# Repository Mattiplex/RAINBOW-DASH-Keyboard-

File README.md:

# RAINBOW-DASH-KEYBOARD-
A MLP theme KEYBOARD !!!

oh yeah , watch me take on this four day challenge to create this keyboard with no experience. (editing matthew here) so keeb got extended but i miss the deadline so im shipping to STARDANCE. oh well stardance has ended also well better luck at fabricate !!!

# The What,Why and What i learn.  
## The WHAT
RAINBOW DASH KEYBOARD is a 75% and TKL Hybrid MLP theme keyboard. this keyboard features 84 mechanical switches with hot swappable socket ,Backlit south facing RGB LED,Rotary Encoder and a 0.91 inch OLED screen.this keyboard is power by 3rd party Pico clone board with usb-c port. i also design a custom Case that uses a bottom mount system, The case will be 3d printed with FDM technology Using PETG and be painted later using spray paint. The plate will be fabricated using aluminum 6061-T6 Alloy and have an anodized blue and glass bead sanding finish.There's also a custom Knob that will be printed using PLA.

## The WHY   
so this is my first keyboard, so i decide to challenge myself to create something that's distinctly me. something that other people doesn't have and that is functional so a keyboard is fun little challenge.i want to be able look at me keyboard and be reminded of the countless night i spend making this keyboard.  

## What have i LEARN ?  
i learn lots of stuff, first of all is to do tons of research before going through something you're not familiar with. i also how to make a keyboard , how to plan your keyboard before hand so you don't mess up later in your PCB phase. (i learn all of these the hard way).
CAD is a bit harder for me because im such a perfectionist. but everything gets better with the flow of time as you gain experience. now the KEYWORD here is failing. during the whole length of this project , i fail a lot and that's how i learn ,you learn by failing and trying again.

# The PCB 

# The Case 

i used Bottom style mount to house my pcb , since i think it's the most balance layout between sound , cost and complexity . i also made the plate to integrate inside the bottom case so the plate would sit flush in the case. 
* Bottom Case: PLA WHITE
* TOP Case : PLA WHITE
* KEYBOARD PLATE : Laser Cut Aluminum (anodized blue + bead blast)
* CUSTOM Knob : PLA WHITE

# README
3D PRINTING : PRINTING LEGION @raahicheda4 (SG)

# ASSEMBLY Video

# Time   

  | no | desc | Time taken |  
  | -- | ---- | -----------|  
  | 1. | first design session | 14Hour 33Min 58 Sec |   
  | 2. | second design session | 22Hour 17Min 35Sec |  
  | 3. | CAD design session | 24Hour 27Min 46Sec |  
  | 4. | prepping model and inspection | 39Min |
  | - | total time | 62Hour 12Min 58Sec | 

# price 

| No | DESC | USD | 
| -- | ---- | --- |
| 1. | PCB Board (5 piece)| 21.23USD | 
| 1. | 0805 SMD Cap (20 Piece) ELEMENT14 | 6.02$ | 
| 2. | Kalih Hot Swappable socket (110pc) | 6.06$ |
| 3. | 330R resistor 100pc | 1.12$ |
| 4. | 4700R resistor 100pc | 2.45$ |
| 5. | MCP23017 DIP28 2pc | 6.02$ |
| 6. | EC11 Rotary Encoder 1pc | 0.73$ |
| 7. | M2 Heatset Insert L 3mm 50pc  | 1.41$ |
| 8. | M3 Heatset Insert L 3mm 50pc  | 1.47$ |
| 9. | HZYUEGOU M2 hex wafer head screw  5mm 50pc  | 0.94$ |
| 10. | HZUEGOU M3 hex Wafer head screw 20mm 25pc  |  1.11$ |
| 11. | 1N4148 0805 SOD-323 diode 100pc |  0.95$ |
| 12. | SK6812 MINi-E RGB reverse mount 100pc | 5.71$ |
| 13. | Third party Pi-Pico with Usb-c 1pc | 2.57$ |
| 14. | 0.91inch OLED SCREEN 1pc  | 2.36$ |
| 15. | 1mm transparent acrylic sheet 1 pc | 0.92$ |
| 1. | Jaycomia Rainbow PBT Keycaps Set | 20.37$ |
| 2. | Kalih Box Jade Tactile switch (90pc) | 20.49$ |
| 3. | Durock Stabilizer V3 set 4(2u) 1(6.25u) | 18.26$ |
| 4. | Fancy rainbow coiled Usb-C cable with aviator connector | 7.97$ |
| 3. | Shipping Fee (ALIEXPRESS) | 1.58$ |
| 4. | Shipping Fee (ELEMENT14) | None |
| 5. | TAX (ALIEXPRESS) | 10.93$ | 
| 6. | Extra 5$ for daily price fluctuation Aliexpress | 5$ | 
| 1. | Top Case,bottom case & custom knob (Printing Legion) | 30$ |
| 2. | aluminum Plate (PCBWAY) | 39.77$ | 
| 3. | shipping Fee (Printing Legion) | 10$ |
| 4. | shipping Fee (PCBWAY) | none (air freight) |   
| - | Total | 225.44$ | 

## excluded stuff (coz it's expensive enough alr)
* spray paint & primer 
* high grit sand paper 
* solder and flux

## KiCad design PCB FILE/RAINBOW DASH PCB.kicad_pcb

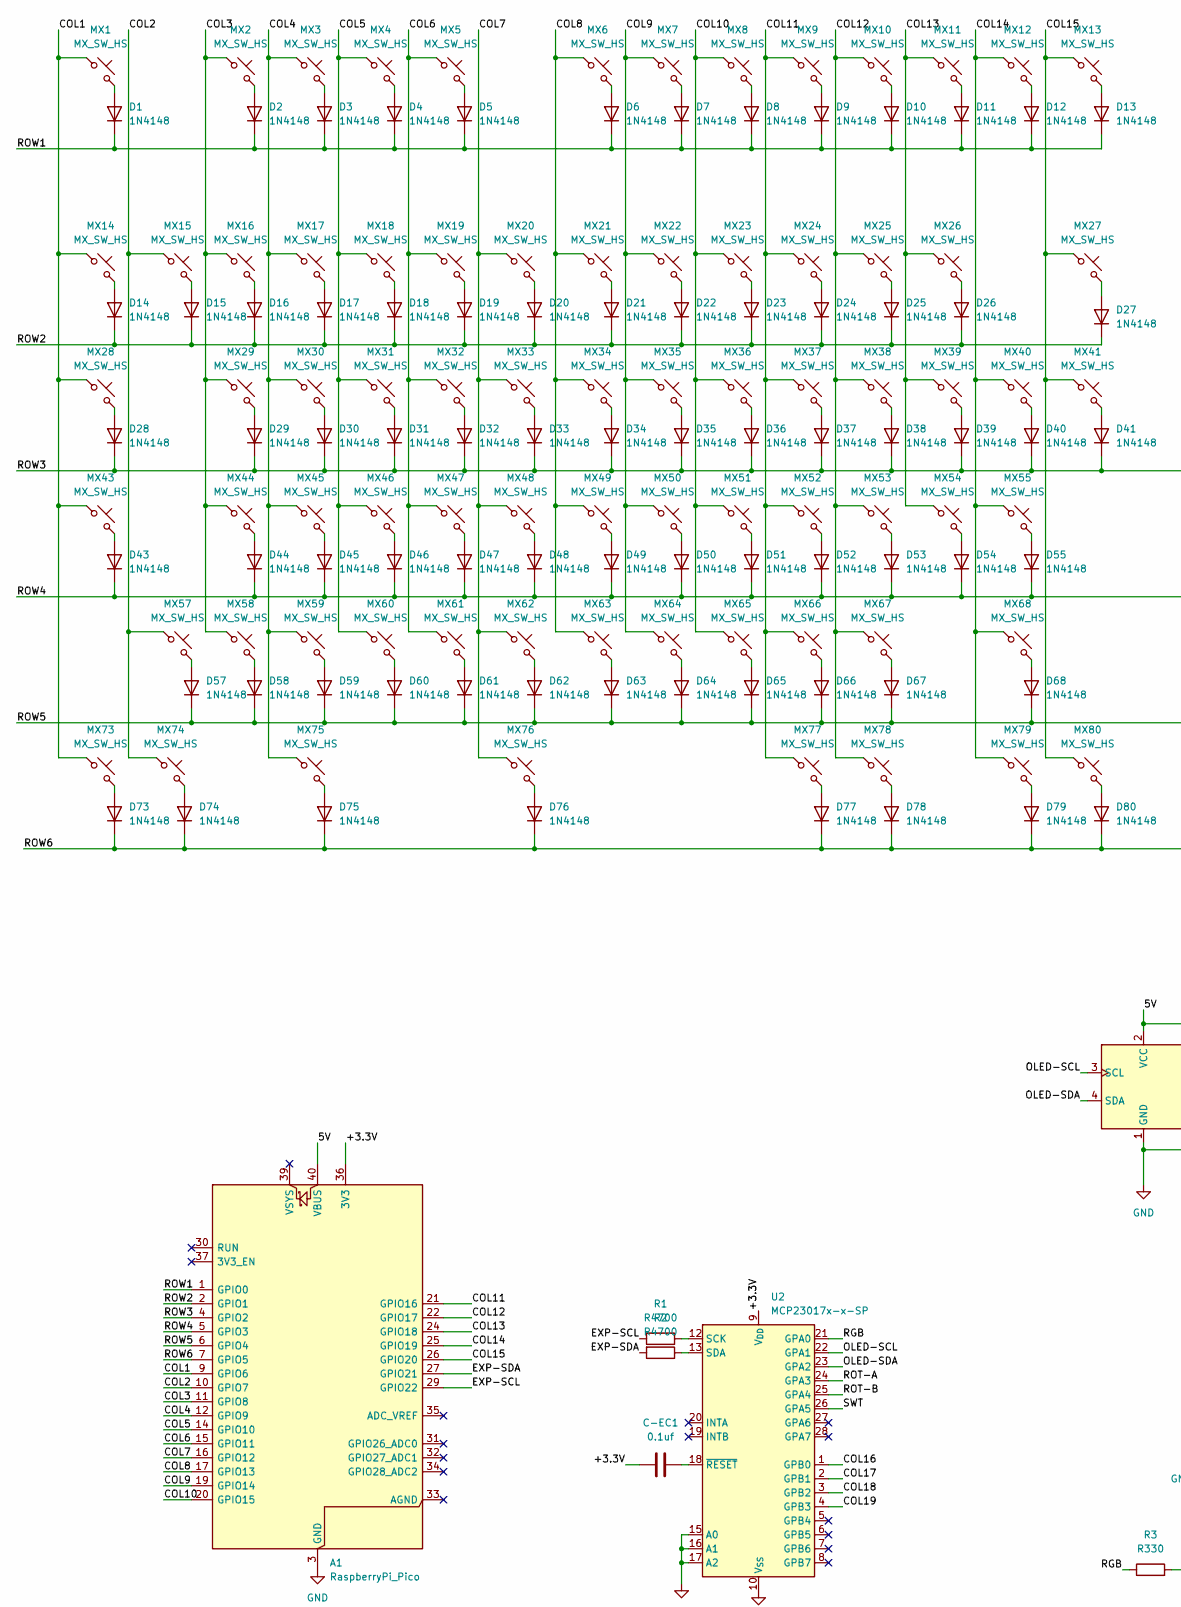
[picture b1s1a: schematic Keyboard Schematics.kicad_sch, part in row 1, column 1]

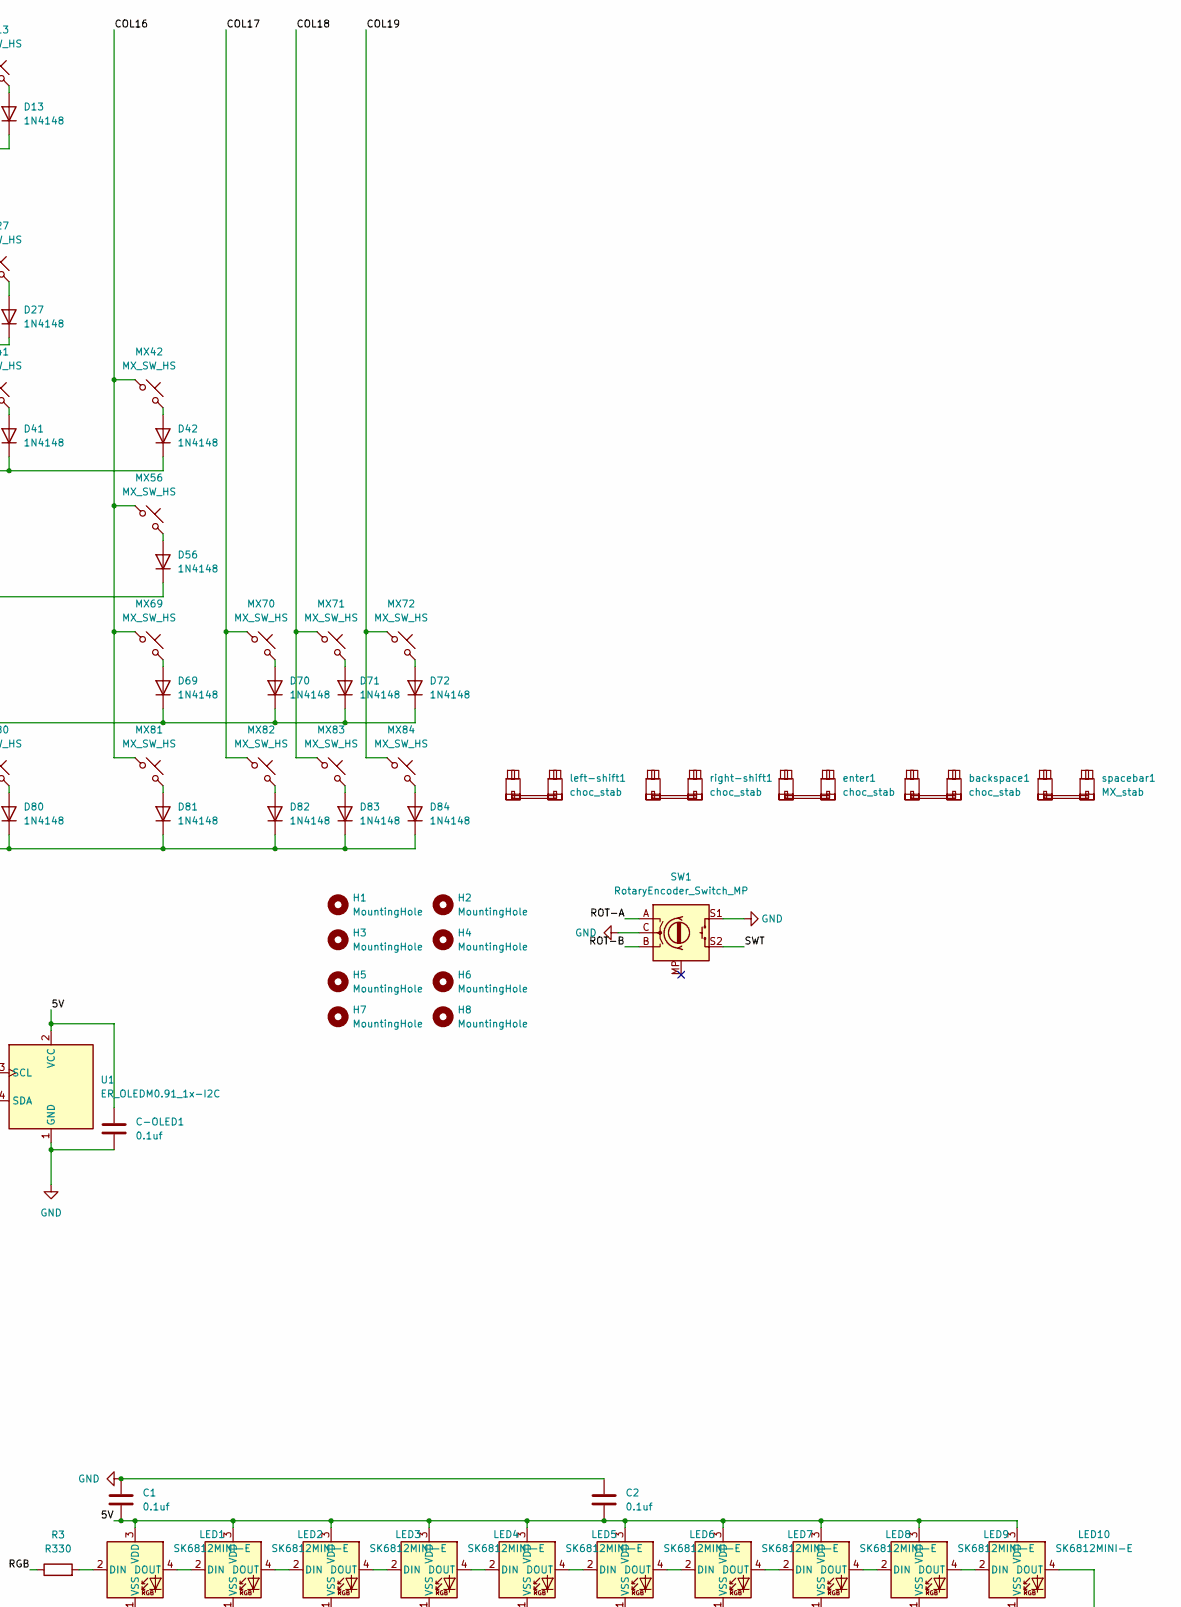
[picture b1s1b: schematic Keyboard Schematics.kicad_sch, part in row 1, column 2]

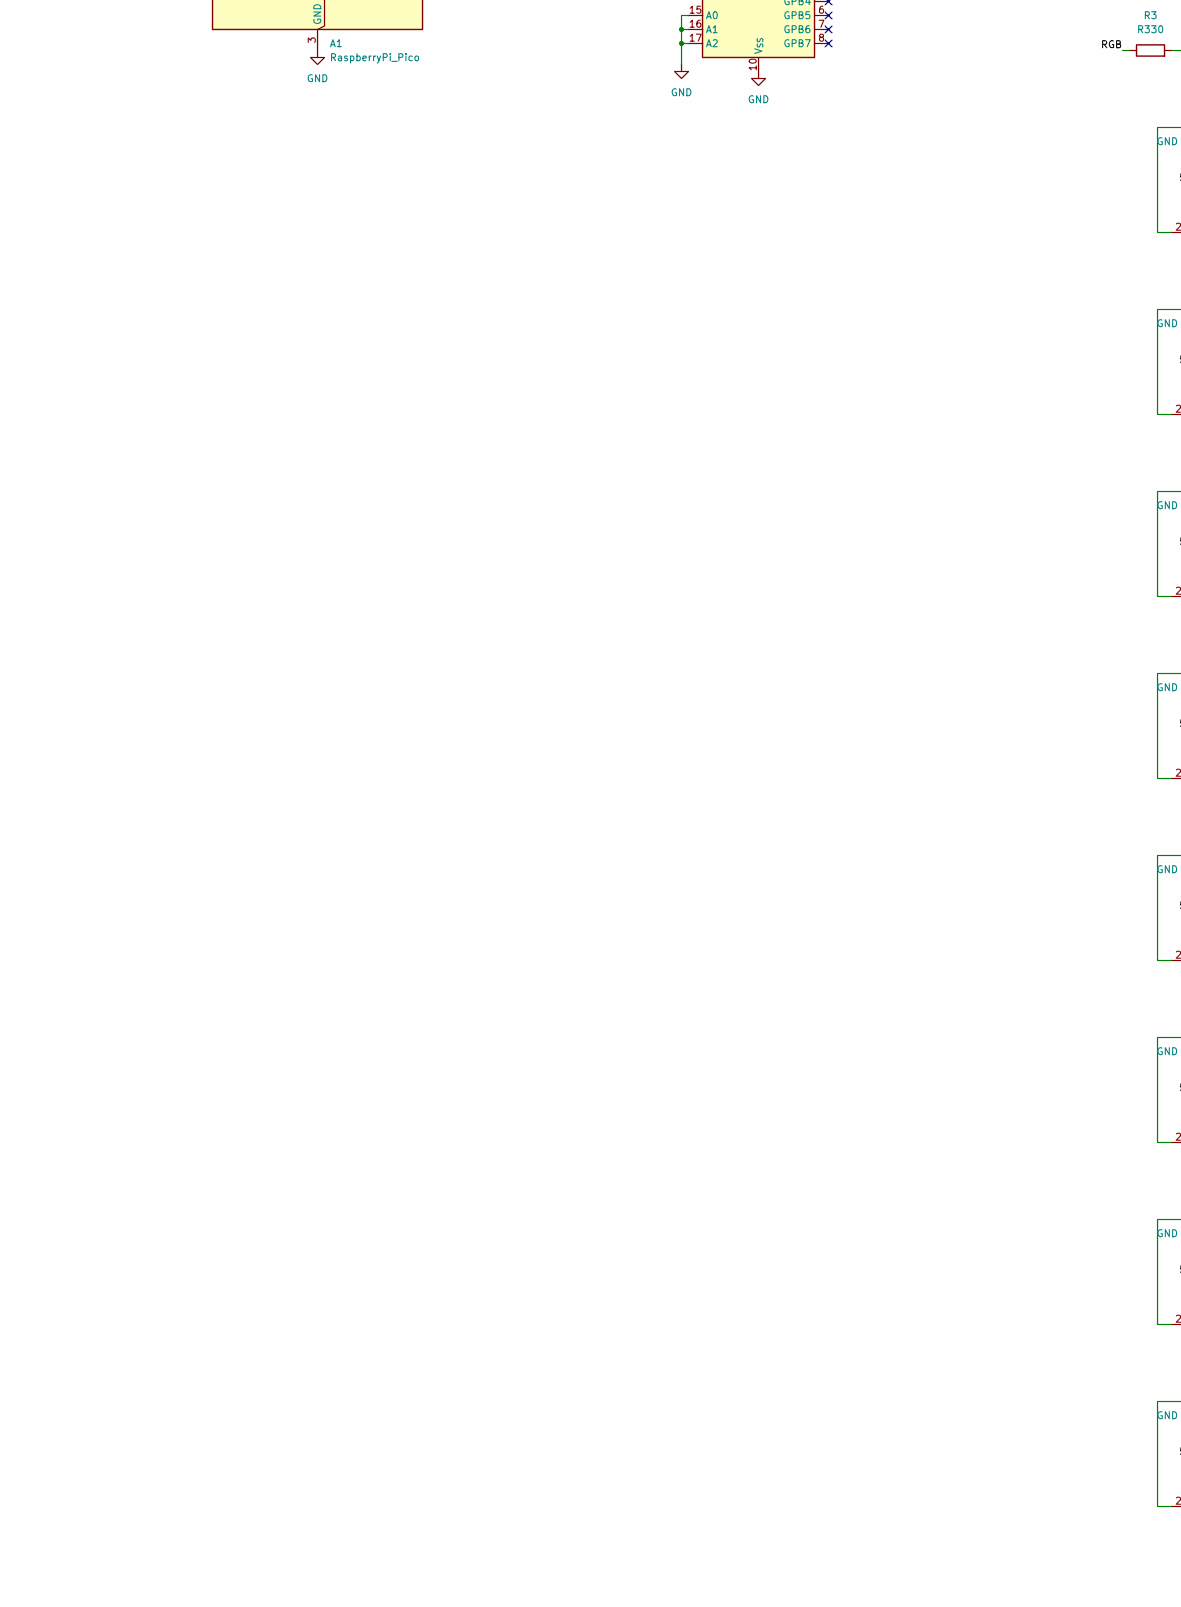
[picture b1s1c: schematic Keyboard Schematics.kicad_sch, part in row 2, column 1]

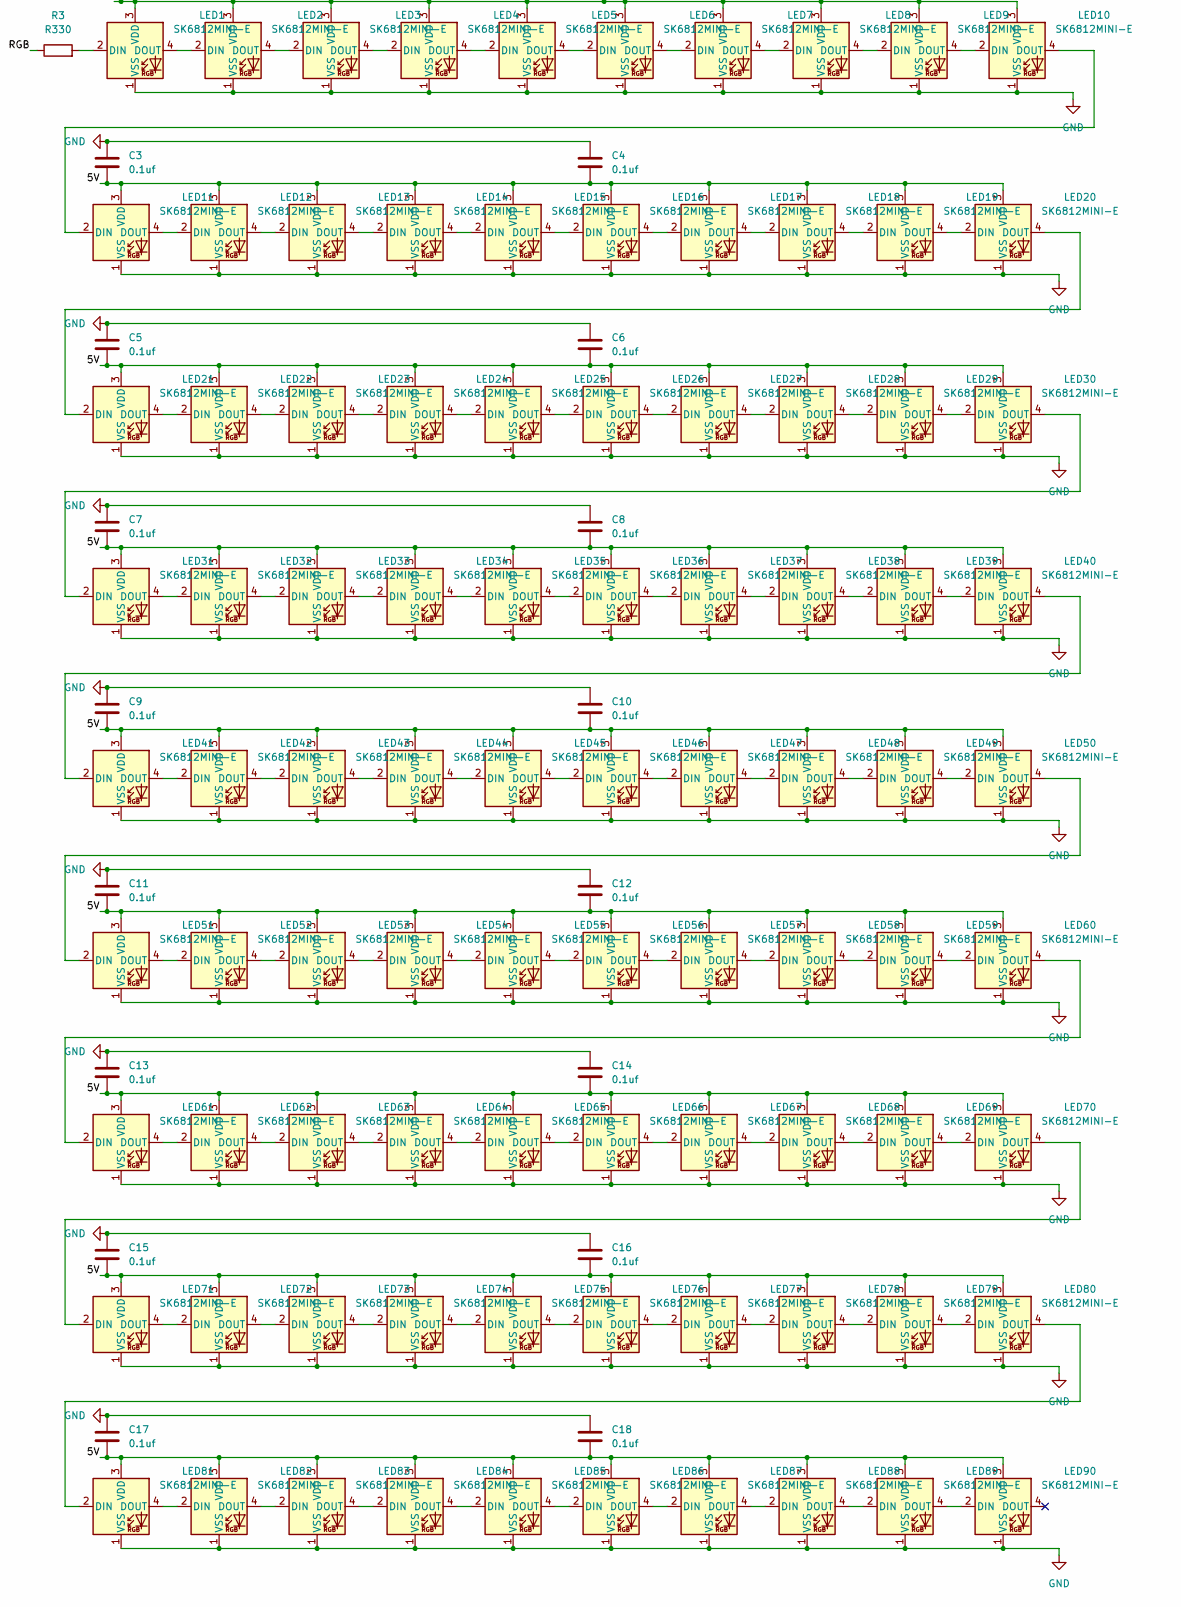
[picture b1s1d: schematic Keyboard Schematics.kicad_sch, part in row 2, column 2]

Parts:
A1: RaspberryPi_Pico; RaspberryPi_Pico_Common_THT
C1, C2, C3, C4, C5, C6, C7, C8, C9, C10, C11, C12, C13, C14, C15, C16, C17, C18: 0.1uf; C_0805_2012Metric_Pad1.18x1.45mm_HandSolder
C-EC1: 0.1uf; C_0805_2012Metric_Pad1.18x1.45mm_HandSolder
C-OLED1: 0.1uf; C_0805_2012Metric_Pad1.18x1.45mm_HandSolder
D1, D2, D3, D4, D5, D6, D7, D8, D9, D10, D11, D12, D13, D14, D15, D16, D17, D18, D19, D20, D21, D22, D23, D24, D25, D26, D27, D28, D29, D30, D31, D32, D33, D34, D35, D36, D37, D38, D39, D40, D41, D42, D43, D44, D45, D46, D47, D48, D49, D50, D51, D52, D53, D54, D55, D56, D57, D58, D59, D60, D61, D62, D63, D64, D65, D66, D67, D68, D69, D70, D71, D72, D73, D74, D75, D76, D77, D78, D79, D80, D81, D82, D83, D84: 1N4148; D_0805_2012Metric
H1, H2, H3, H4, H5, H6, H7, H8: MountingHole; MountingHole_2.2mm_M2
LED1, LED2, LED3, LED4, LED5, LED6, LED7, LED8, LED9, LED10, LED11, LED12, LED13, LED14, LED15, LED16, LED17, LED18, LED19, LED20, LED21, LED22, LED23, LED24, LED25, LED26, LED27, LED28, LED29, LED30, LED31, LED32, LED33, LED34, LED35, LED36, LED37, LED38, LED39, LED40, LED41, LED42, LED43, LED44, LED45, LED46, LED47, LED48, LED49, LED50, LED51, LED52, LED53, LED54, LED55, LED56, LED57, LED58, LED59, LED60, LED61, LED62, LED63, LED64, LED65, LED66, LED67, LED68, LED69, LED70, LED71, LED72, LED73, LED74, LED75, LED76, LED77, LED78, LED79, LED80, LED81, LED82, LED83, LED84, LED85, LED86, LED87, LED88, LED89, LED90: SK6812MINI-E; LED_SK6812MINI-E_3.2x2.8mm_P1.5mm_ReverseMount
MX1, MX2, MX3, MX4, MX5, MX6, MX7, MX8, MX9, MX10, MX11, MX12, MX13, MX14, MX15, MX16, MX17, MX18, MX19, MX20, MX21, MX22, MX23, MX24, MX25, MX26, MX27, MX28, MX29, MX30, MX31, MX32, MX33, MX34, MX35, MX36, MX37, MX38, MX39, MX40, MX41, MX42, MX43, MX44, MX45, MX46, MX47, MX48, MX49, MX50, MX51, MX52, MX53, MX54, MX55, MX56, MX57, MX58, MX59, MX60, MX61, MX62, MX63, MX64, MX65, MX66, MX67, MX68, MX69, MX70, MX71, MX72, MX73, MX74, MX75, MX76, MX77, MX78, MX79, MX80, MX81, MX82, MX83, MX84: MX_SW_HS; SW_MX_HS_CPG151101S11_1u
R1, R2: R4700; R_Axial_DIN0207_L6.3mm_D2.5mm_P10.16mm_Horizontal
R3: R330; R_Axial_DIN0207_L6.3mm_D2.5mm_P10.16mm_Horizontal
SW1: RotaryEncoder_Switch_MP; ROT_Alps_EC11E-Switch
U1: ER_OLEDM0.91_1x-I2C
U2: MCP23017x-x-SP; DIP-28_W7.62mm_LongPads
backspace1: choc_stab; STAB_MX_2u
enter1: choc_stab; STAB_MX_2.25u
left-shift1: choc_stab; STAB_MX_2.25u
right-shift1: choc_stab; STAB_MX_2.75u
spacebar1: MX_stab; STAB_MX_6.25u

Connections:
/5V: A1.40 (VBUS), C1.1, C2.1, C3.1, C4.1, C5.1, C6.1, C7.1, C8.1, C9.1, C10.1, C11.1, C12.1, C13.1, C14.1, C15.1, C16.1, C17.1, C18.1, C-OLED1.1, LED1.3 (VDD), LED2.3 (VDD), LED3.3 (VDD), LED4.3 (VDD), LED5.3 (VDD), LED6.3 (VDD), LED7.3 (VDD), LED8.3 (VDD), LED9.3 (VDD), LED10.3 (VDD), LED11.3 (VDD), LED12.3 (VDD), LED13.3 (VDD), LED14.3 (VDD), LED15.3 (VDD), LED16.3 (VDD), LED17.3 (VDD), LED18.3 (VDD), LED19.3 (VDD), LED20.3 (VDD), LED21.3 (VDD), LED22.3 (VDD), LED23.3 (VDD), LED24.3 (VDD), LED25.3 (VDD), LED26.3 (VDD), LED27.3 (VDD), LED28.3 (VDD), LED29.3 (VDD), LED30.3 (VDD), LED31.3 (VDD), LED32.3 (VDD), LED33.3 (VDD), LED34.3 (VDD), LED35.3 (VDD), LED36.3 (VDD), LED37.3 (VDD), LED38.3 (VDD), LED39.3 (VDD), LED40.3 (VDD), LED41.3 (VDD), LED42.3 (VDD), LED43.3 (VDD), LED44.3 (VDD), LED45.3 (VDD), LED46.3 (VDD), LED47.3 (VDD), LED48.3 (VDD), LED49.3 (VDD), LED50.3 (VDD), LED51.3 (VDD), LED52.3 (VDD), LED53.3 (VDD), LED54.3 (VDD), LED55.3 (VDD), LED56.3 (VDD), LED57.3 (VDD), LED58.3 (VDD), LED59.3 (VDD), LED60.3 (VDD), LED61.3 (VDD), LED62.3 (VDD), LED63.3 (VDD), LED64.3 (VDD), LED65.3 (VDD), LED66.3 (VDD), LED67.3 (VDD), LED68.3 (VDD), LED69.3 (VDD), LED70.3 (VDD), LED71.3 (VDD), LED72.3 (VDD), LED73.3 (VDD), LED74.3 (VDD), LED75.3 (VDD), LED76.3 (VDD), LED77.3 (VDD), LED78.3 (VDD), LED79.3 (VDD), LED80.3 (VDD), LED81.3 (VDD), LED82.3 (VDD), LED83.3 (VDD), LED84.3 (VDD), LED85.3 (VDD), LED86.3 (VDD), LED87.3 (VDD), LED88.3 (VDD), LED89.3 (VDD), LED90.3 (VDD), U1.2 (VCC)
/+3.3V: A1.36 (3V3), C-EC1.1, U2.9 (V_{DD})
/COL1: A1.9 (GPIO6), MX1.1, MX14.1, MX28.1, MX43.1, MX73.1
/COL2: A1.10 (GPIO7), MX15.1, MX57.1, MX74.1
/COL3: A1.11 (GPIO8), MX2.1, MX16.1, MX29.1, MX44.1, MX58.1
/COL4: A1.12 (GPIO9), MX3.1, MX17.1, MX30.1, MX45.1, MX59.1, MX75.1
/COL5: A1.14 (GPIO10), MX4.1, MX18.1, MX31.1, MX46.1, MX60.1
/COL6: A1.15 (GPIO11), MX5.1, MX19.1, MX32.1, MX47.1, MX61.1
/COL7: A1.16 (GPIO12), MX20.1, MX33.1, MX48.1, MX62.1, MX76.1
/COL8: A1.17 (GPIO13), MX6.1, MX21.1, MX34.1, MX49.1, MX63.1
/COL9: A1.19 (GPIO14), MX7.1, MX22.1, MX35.1, MX50.1, MX64.1
/COL10: A1.20 (GPIO15), MX8.1, MX23.1, MX36.1, MX51.1, MX65.1
/COL11: A1.21 (GPIO16), MX9.1, MX24.1, MX37.1, MX52.1, MX66.1, MX77.1
/COL12: A1.22 (GPIO17), MX10.1, MX25.1, MX38.1, MX53.1, MX67.1, MX78.1
/COL13: A1.24 (GPIO18), MX11.1, MX26.1, MX39.1, MX54.1
/COL14: A1.25 (GPIO19), MX12.1, MX40.1, MX55.1, MX68.1, MX79.1
/COL15: A1.26 (GPIO20), MX13.1, MX27.1, MX41.1, MX80.1
/COL16: MX42.1, MX56.1, MX69.1, MX81.1, U2.1 (GPB0)
/COL17: MX70.1, MX82.1, U2.2 (GPB1)
/COL18: MX71.1, MX83.1, U2.3 (GPB2)
/COL19: MX72.1, MX84.1, U2.4 (GPB3)
/EXP-SCL: A1.29 (GPIO22), R1.2
/EXP-SDA: A1.27 (GPIO21), R2.2
/OLED-SCL: U1.3 (SCL), U2.22 (GPA1)
/OLED-SDA: U1.4 (SDA), U2.23 (GPA2)
/RGB: R3.1, U2.21 (GPA0)
/ROT-A: SW1.A, U2.24 (GPA3)
/ROT-B: SW1.B, U2.25 (GPA4)
/ROW1: A1.1 (GPIO0), D1.1 (K), D2.1 (K), D3.1 (K), D4.1 (K), D5.1 (K), D6.1 (K), D7.1 (K), D8.1 (K), D9.1 (K), D10.1 (K), D11.1 (K), D12.1 (K), D13.1 (K)
/ROW2: A1.2 (GPIO1), D14.1 (K), D15.1 (K), D16.1 (K), D17.1 (K), D18.1 (K), D19.1 (K), D20.1 (K), D21.1 (K), D22.1 (K), D23.1 (K), D24.1 (K), D25.1 (K), D26.1 (K), D27.1 (K)
/ROW3: A1.4 (GPIO2), D28.1 (K), D29.1 (K), D30.1 (K), D31.1 (K), D32.1 (K), D33.1 (K), D34.1 (K), D35.1 (K), D36.1 (K), D37.1 (K), D38.1 (K), D39.1 (K), D40.1 (K), D41.1 (K), D42.1 (K)
/ROW4: A1.5 (GPIO3), D43.1 (K), D44.1 (K), D45.1 (K), D46.1 (K), D47.1 (K), D48.1 (K), D49.1 (K), D50.1 (K), D51.1 (K), D52.1 (K), D53.1 (K), D54.1 (K), D55.1 (K), D56.1 (K)
/ROW5: A1.6 (GPIO4), D57.1 (K), D58.1 (K), D59.1 (K), D60.1 (K), D61.1 (K), D62.1 (K), D63.1 (K), D64.1 (K), D65.1 (K), D66.1 (K), D67.1 (K), D68.1 (K), D69.1 (K), D70.1 (K), D71.1 (K), D72.1 (K)
/ROW6: A1.7 (GPIO5), D73.1 (K), D74.1 (K), D75.1 (K), D76.1 (K), D77.1 (K), D78.1 (K), D79.1 (K), D80.1 (K), D81.1 (K), D82.1 (K), D83.1 (K), D84.1 (K)
/SWT: SW1.S2, U2.26 (GPA5)
GND: A1.3 (GND), A1.8 (GND), A1.13 (GND), A1.18 (GND), A1.23 (GND), A1.28 (GND), A1.38 (GND), C1.2, C2.2, C3.2, C4.2, C5.2, C6.2, C7.2, C8.2, C9.2, C10.2, C11.2, C12.2, C13.2, C14.2, C15.2, C16.2, C17.2, C18.2, C-OLED1.2, LED1.1 (VSS), LED2.1 (VSS), LED3.1 (VSS), LED4.1 (VSS), LED5.1 (VSS), LED6.1 (VSS), LED7.1 (VSS), LED8.1 (VSS), LED9.1 (VSS), LED10.1 (VSS), LED11.1 (VSS), LED12.1 (VSS), LED13.1 (VSS), LED14.1 (VSS), LED15.1 (VSS), LED16.1 (VSS), LED17.1 (VSS), LED18.1 (VSS), LED19.1 (VSS), LED20.1 (VSS), LED21.1 (VSS), LED22.1 (VSS), LED23.1 (VSS), LED24.1 (VSS), LED25.1 (VSS), LED26.1 (VSS), LED27.1 (VSS), LED28.1 (VSS), LED29.1 (VSS), LED30.1 (VSS), LED31.1 (VSS), LED32.1 (VSS), LED33.1 (VSS), LED34.1 (VSS), LED35.1 (VSS), LED36.1 (VSS), LED37.1 (VSS), LED38.1 (VSS), LED39.1 (VSS), LED40.1 (VSS), LED41.1 (VSS), LED42.1 (VSS), LED43.1 (VSS), LED44.1 (VSS), LED45.1 (VSS), LED46.1 (VSS), LED47.1 (VSS), LED48.1 (VSS), LED49.1 (VSS), LED50.1 (VSS), LED51.1 (VSS), LED52.1 (VSS), LED53.1 (VSS), LED54.1 (VSS), LED55.1 (VSS), LED56.1 (VSS), LED57.1 (VSS), LED58.1 (VSS), LED59.1 (VSS), LED60.1 (VSS), LED61.1 (VSS), LED62.1 (VSS), LED63.1 (VSS), LED64.1 (VSS), LED65.1 (VSS), LED66.1 (VSS), LED67.1 (VSS), LED68.1 (VSS), LED69.1 (VSS), LED70.1 (VSS), LED71.1 (VSS), LED72.1 (VSS), LED73.1 (VSS), LED74.1 (VSS), LED75.1 (VSS), LED76.1 (VSS), LED77.1 (VSS), LED78.1 (VSS), LED79.1 (VSS), LED80.1 (VSS), LED81.1 (VSS), LED82.1 (VSS), LED83.1 (VSS), LED84.1 (VSS), LED85.1 (VSS), LED86.1 (VSS), LED87.1 (VSS), LED88.1 (VSS), LED89.1 (VSS), LED90.1 (VSS), SW1.C, SW1.S1, U1.1 (GND), U2.10 (V_{SS}), U2.15 (A0), U2.16 (A1), U2.17 (A2)
unnamed: D1.2 (A), MX1.2
unnamed: D2.2 (A), MX2.2
unnamed: D3.2 (A), MX3.2
unnamed: D4.2 (A), MX4.2
unnamed: D5.2 (A), MX5.2
unnamed: D6.2 (A), MX6.2
unnamed: D7.2 (A), MX7.2
unnamed: D8.2 (A), MX8.2
unnamed: D9.2 (A), MX9.2
unnamed: D10.2 (A), MX10.2
unnamed: D11.2 (A), MX11.2
unnamed: D12.2 (A), MX12.2
unnamed: D13.2 (A), MX13.2
unnamed: D14.2 (A), MX14.2
unnamed: D15.2 (A), MX15.2
unnamed: D16.2 (A), MX16.2
unnamed: D17.2 (A), MX17.2
unnamed: D18.2 (A), MX18.2
unnamed: D19.2 (A), MX19.2
unnamed: D20.2 (A), MX20.2
unnamed: D21.2 (A), MX21.2
unnamed: D22.2 (A), MX22.2
unnamed: D23.2 (A), MX23.2
unnamed: D24.2 (A), MX24.2
unnamed: D25.2 (A), MX25.2
unnamed: D26.2 (A), MX26.2
unnamed: D27.2 (A), MX27.2
unnamed: D28.2 (A), MX28.2
unnamed: D29.2 (A), MX29.2
unnamed: D30.2 (A), MX30.2
unnamed: D31.2 (A), MX31.2
unnamed: D32.2 (A), MX32.2
unnamed: D33.2 (A), MX33.2
unnamed: D34.2 (A), MX34.2
unnamed: D35.2 (A), MX35.2
unnamed: D36.2 (A), MX36.2
unnamed: D37.2 (A), MX37.2
unnamed: D38.2 (A), MX38.2
unnamed: D39.2 (A), MX39.2
unnamed: D40.2 (A), MX40.2
unnamed: D41.2 (A), MX41.2
unnamed: D42.2 (A), MX42.2
unnamed: D43.2 (A), MX43.2
unnamed: D44.2 (A), MX44.2
unnamed: D45.2 (A), MX45.2
unnamed: D46.2 (A), MX46.2
unnamed: D47.2 (A), MX47.2
unnamed: D48.2 (A), MX48.2
unnamed: D49.2 (A), MX49.2
unnamed: D50.2 (A), MX50.2
unnamed: D51.2 (A), MX51.2
unnamed: D52.2 (A), MX52.2
unnamed: D53.2 (A), MX53.2
unnamed: D54.2 (A), MX54.2
unnamed: D55.2 (A), MX55.2
unnamed: D56.2 (A), MX56.2
unnamed: D57.2 (A), MX57.2
unnamed: D58.2 (A), MX58.2
unnamed: D59.2 (A), MX59.2
unnamed: D60.2 (A), MX60.2
unnamed: D61.2 (A), MX61.2
unnamed: D62.2 (A), MX62.2
unnamed: D63.2 (A), MX63.2
unnamed: D64.2 (A), MX64.2
unnamed: D65.2 (A), MX65.2
unnamed: D66.2 (A), MX66.2
unnamed: D67.2 (A), MX67.2
unnamed: D68.2 (A), MX68.2
unnamed: D69.2 (A), MX69.2
unnamed: D70.2 (A), MX70.2
unnamed: D71.2 (A), MX71.2
unnamed: D72.2 (A), MX72.2
unnamed: D73.2 (A), MX73.2
unnamed: D74.2 (A), MX74.2
unnamed: D75.2 (A), MX75.2
unnamed: D76.2 (A), MX76.2
unnamed: D77.2 (A), MX77.2
unnamed: D78.2 (A), MX78.2
unnamed: D79.2 (A), MX79.2
unnamed: D80.2 (A), MX80.2
unnamed: D81.2 (A), MX81.2
unnamed: D82.2 (A), MX82.2
unnamed: D83.2 (A), MX83.2
unnamed: D84.2 (A), MX84.2
unnamed: LED1.2 (DIN), R3.2
unnamed: LED1.4 (DOUT), LED2.2 (DIN)
unnamed: LED2.4 (DOUT), LED3.2 (DIN)
unnamed: LED3.4 (DOUT), LED4.2 (DIN)
unnamed: LED4.4 (DOUT), LED5.2 (DIN)
unnamed: LED5.4 (DOUT), LED6.2 (DIN)
unnamed: LED6.4 (DOUT), LED7.2 (DIN)
unnamed: LED7.4 (DOUT), LED8.2 (DIN)
unnamed: LED8.4 (DOUT), LED9.2 (DIN)
unnamed: LED9.4 (DOUT), LED10.2 (DIN)
unnamed: LED10.4 (DOUT), LED11.2 (DIN)
unnamed: LED11.4 (DOUT), LED12.2 (DIN)
unnamed: LED12.4 (DOUT), LED13.2 (DIN)
unnamed: LED13.4 (DOUT), LED14.2 (DIN)
unnamed: LED14.4 (DOUT), LED15.2 (DIN)
unnamed: LED15.4 (DOUT), LED16.2 (DIN)
unnamed: LED16.4 (DOUT), LED17.2 (DIN)
unnamed: LED17.4 (DOUT), LED18.2 (DIN)
unnamed: LED18.4 (DOUT), LED19.2 (DIN)
unnamed: LED19.4 (DOUT), LED20.2 (DIN)
unnamed: LED20.4 (DOUT), LED21.2 (DIN)
unnamed: LED21.4 (DOUT), LED22.2 (DIN)
unnamed: LED22.4 (DOUT), LED23.2 (DIN)
unnamed: LED23.4 (DOUT), LED24.2 (DIN)
unnamed: LED24.4 (DOUT), LED25.2 (DIN)
unnamed: LED25.4 (DOUT), LED26.2 (DIN)
unnamed: LED26.4 (DOUT), LED27.2 (DIN)
unnamed: LED27.4 (DOUT), LED28.2 (DIN)
unnamed: LED28.4 (DOUT), LED29.2 (DIN)
unnamed: LED29.4 (DOUT), LED30.2 (DIN)
unnamed: LED30.4 (DOUT), LED31.2 (DIN)
unnamed: LED31.4 (DOUT), LED32.2 (DIN)
unnamed: LED32.4 (DOUT), LED33.2 (DIN)
unnamed: LED33.4 (DOUT), LED34.2 (DIN)
unnamed: LED34.4 (DOUT), LED35.2 (DIN)
unnamed: LED35.4 (DOUT), LED36.2 (DIN)
unnamed: LED36.4 (DOUT), LED37.2 (DIN)
unnamed: LED37.4 (DOUT), LED38.2 (DIN)
unnamed: LED38.4 (DOUT), LED39.2 (DIN)
unnamed: LED39.4 (DOUT), LED40.2 (DIN)
unnamed: LED40.4 (DOUT), LED41.2 (DIN)
unnamed: LED41.4 (DOUT), LED42.2 (DIN)
unnamed: LED42.4 (DOUT), LED43.2 (DIN)
unnamed: LED43.4 (DOUT), LED44.2 (DIN)
unnamed: LED44.4 (DOUT), LED45.2 (DIN)
unnamed: LED45.4 (DOUT), LED46.2 (DIN)
unnamed: LED46.4 (DOUT), LED47.2 (DIN)
unnamed: LED47.4 (DOUT), LED48.2 (DIN)
unnamed: LED48.4 (DOUT), LED49.2 (DIN)
unnamed: LED49.4 (DOUT), LED50.2 (DIN)
unnamed: LED50.4 (DOUT), LED51.2 (DIN)
unnamed: LED51.4 (DOUT), LED52.2 (DIN)
unnamed: LED52.4 (DOUT), LED53.2 (DIN)
unnamed: LED53.4 (DOUT), LED54.2 (DIN)
unnamed: LED54.4 (DOUT), LED55.2 (DIN)
unnamed: LED55.4 (DOUT), LED56.2 (DIN)
unnamed: LED56.4 (DOUT), LED57.2 (DIN)
unnamed: LED57.4 (DOUT), LED58.2 (DIN)
unnamed: LED58.4 (DOUT), LED59.2 (DIN)
unnamed: LED59.4 (DOUT), LED60.2 (DIN)
unnamed: LED60.4 (DOUT), LED61.2 (DIN)
unnamed: LED61.4 (DOUT), LED62.2 (DIN)
unnamed: LED62.4 (DOUT), LED63.2 (DIN)
unnamed: LED63.4 (DOUT), LED64.2 (DIN)
unnamed: LED64.4 (DOUT), LED65.2 (DIN)
unnamed: LED65.4 (DOUT), LED66.2 (DIN)
unnamed: LED66.4 (DOUT), LED67.2 (DIN)
unnamed: LED67.4 (DOUT), LED68.2 (DIN)
unnamed: LED68.4 (DOUT), LED69.2 (DIN)
unnamed: LED69.4 (DOUT), LED70.2 (DIN)
unnamed: LED70.4 (DOUT), LED71.2 (DIN)
unnamed: LED71.4 (DOUT), LED72.2 (DIN)
unnamed: LED72.4 (DOUT), LED73.2 (DIN)
unnamed: LED73.4 (DOUT), LED74.2 (DIN)
unnamed: LED74.4 (DOUT), LED75.2 (DIN)
unnamed: LED75.4 (DOUT), LED76.2 (DIN)
unnamed: LED76.4 (DOUT), LED77.2 (DIN)
unnamed: LED77.4 (DOUT), LED78.2 (DIN)
unnamed: LED78.4 (DOUT), LED79.2 (DIN)
unnamed: LED79.4 (DOUT), LED80.2 (DIN)
unnamed: LED80.4 (DOUT), LED81.2 (DIN)
unnamed: LED81.4 (DOUT), LED82.2 (DIN)
unnamed: LED82.4 (DOUT), LED83.2 (DIN)
unnamed: LED83.4 (DOUT), LED84.2 (DIN)
unnamed: LED84.4 (DOUT), LED85.2 (DIN)
unnamed: LED85.4 (DOUT), LED86.2 (DIN)
unnamed: LED86.4 (DOUT), LED87.2 (DIN)
unnamed: LED87.4 (DOUT), LED88.2 (DIN)
unnamed: LED88.4 (DOUT), LED89.2 (DIN)
unnamed: LED89.4 (DOUT), LED90.2 (DIN)
unnamed: R1.1, U2.12 (SCK)
unnamed: R2.1, U2.13 (SDA)
unnamed: C-EC1.2, U2.18 (~RESET)

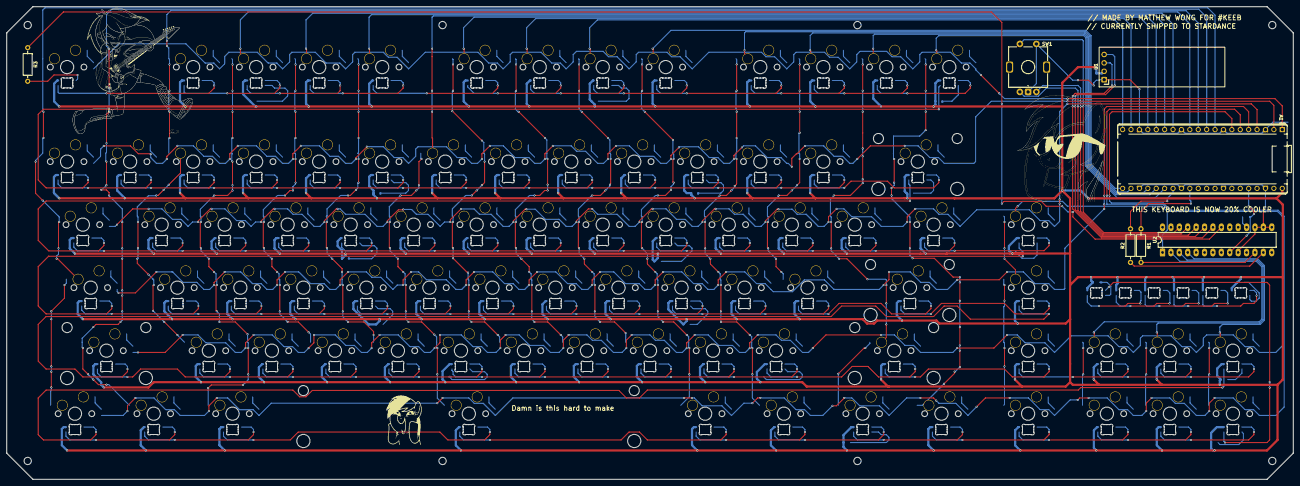
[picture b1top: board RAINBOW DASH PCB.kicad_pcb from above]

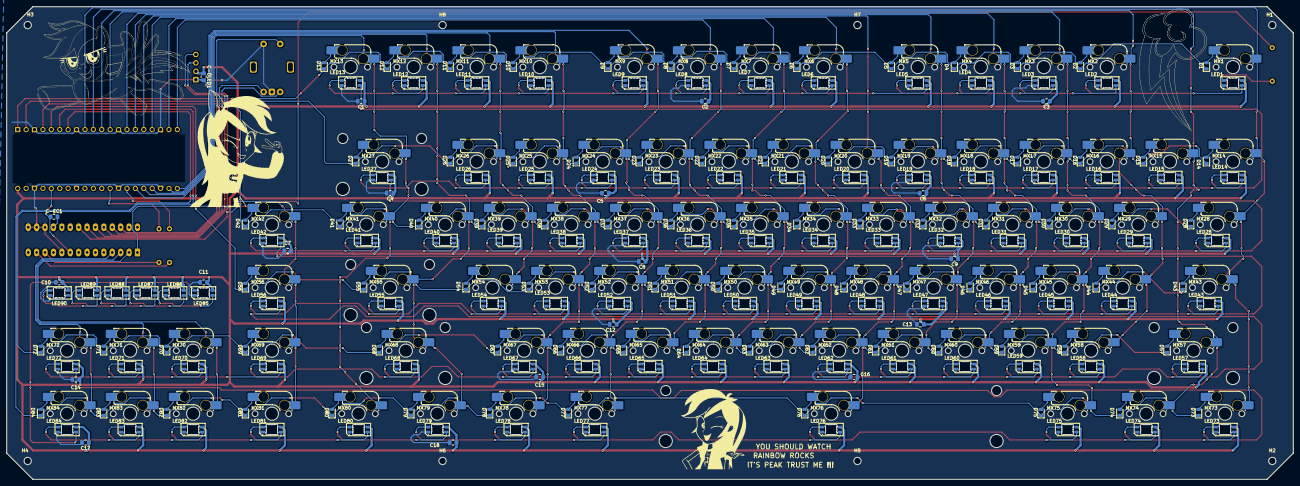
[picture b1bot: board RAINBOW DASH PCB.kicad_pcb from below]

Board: 2 copper layers, 388.9 x 142.9 mm, 298 parts (291 on the bottom side), 213 nets.

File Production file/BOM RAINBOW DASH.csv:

"Id";"Designator";"Footprint";"Quantity";"Designation";"Supplier and ref";
1;"A1";"RaspberryPi_Pico_Common_THT";1;"RaspberryPi_Pico";;;
2;"backspace1";"STAB_MX_2u";1;"choc_stab";;;
3;"C-EC1, C-OLED1, C1, C2, C3, C4, C5, C6, C7, C8, C9, C10, C11, C12, C13, C14, C15, C16, C17, C18";"C_0805_2012Metric_Pad1.18x1.45mm_HandSolder";20;"0.1uf";;;
4;"D1, D2, D3, D4, D5, D6, D7, D8, D9, D10, D11, D12, D13, D14, D15, D16, D17, D18, D19, D20, D21, D22, D23, D24, D25, D26, D27, D28, D29, D30, D31, D32, D33, D34, D35, D36, D37, D38, D39, D40, D41, D42, D43, D44, D45, D46, D47, D48, D49, D50, D51, D52, D53, D54, D55, D56, D57, D58, D59, D60, D61, D62, D63, D64, D65, D66, D67, D68, D69, D70, D71, D72, D73, D74, D75, D76, D77, D78, D79, D80, D81, D82, D83, D84";"D_0805_2012Metric";84;"1N4148";;;
5;"enter1, left-shift1";"STAB_MX_2.25u";2;"choc_stab";;;
6;"LED1, LED2, LED3, LED4, LED5, LED6, LED7, LED8, LED9, LED10, LED11, LED12, LED13, LED14, LED15, LED16, LED17, LED18, LED19, LED20, LED21, LED22, LED23, LED24, LED25, LED26, LED27, LED28, LED29, LED30, LED31, LED32, LED33, LED34, LED35, LED36, LED37, LED38, LED39, LED40, LED41, LED42, LED43, LED44, LED45, LED46, LED47, LED48, LED49, LED50, LED51, LED52, LED53, LED54, LED55, LED56, LED57, LED58, LED59, LED60, LED61, LED62, LED63, LED64, LED65, LED66, LED67, LED68, LED69, LED70, LED71, LED72, LED73, LED74, LED75, LED76, LED77, LED78, LED79, LED80, LED81, LED82, LED83, LED84, LED85, LED86, LED87, LED88, LED89, LED90";"LED_SK6812MINI-E_3.2x2.8mm_P1.5mm_ReverseMount";90;"SK6812MINI-E";;;
7;"MX1, MX2, MX3, MX4, MX5, MX6, MX7, MX8, MX9, MX10, MX11, MX12, MX13, MX14, MX15, MX16, MX17, MX18, MX19, MX20, MX21, MX22, MX23, MX24, MX25, MX26, MX27, MX28, MX29, MX30, MX31, MX32, MX33, MX34, MX35, MX36, MX37, MX38, MX39, MX40, MX41, MX42, MX43, MX44, MX45, MX46, MX47, MX48, MX49, MX50, MX51, MX52, MX53, MX54, MX55, MX56, MX57, MX58, MX59, MX60, MX61, MX62, MX63, MX64, MX65, MX66, MX67, MX68, MX69, MX70, MX71, MX72, MX73, MX74, MX75, MX76, MX77, MX78, MX79, MX80, MX81, MX82, MX83, MX84";"SW_MX_HS_CPG151101S11_1u";84;"MX_SW_HS";;;
8;"R1, R2";"R_Axial_DIN0207_L6.3mm_D2.5mm_P10.16mm_Horizontal";2;"R4700";;;
9;"R3";"R_Axial_DIN0207_L6.3mm_D2.5mm_P10.16mm_Horizontal";1;"R330";;;
10;"right-shift1";"STAB_MX_2.75u";1;"choc_stab";;;
11;"spacebar1";"STAB_MX_6.25u";1;"MX_stab";;;
12;"SW1";"ROT_Alps_EC11E-Switch";1;"RotaryEncoder_Switch_MP";;;
13;"U1";"ER_OLEDM0.91_1x-I2C";1;"ER_OLEDM0.91_1x-I2C";;;
14;"U2";"DIP-28_W7.62mm_LongPads";1;"MCP23017x-x-SP";;;
